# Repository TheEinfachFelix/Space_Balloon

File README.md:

# Space_Balloon

`git submodule update --init --recursive`

https://meshtastic.org/de/docs/hardware/devices/heltec-automation/lora32/peripherals/

## Reticulum Repos

https://github.com/attermann/microReticulum
https://github.com/markqvist/reticulum

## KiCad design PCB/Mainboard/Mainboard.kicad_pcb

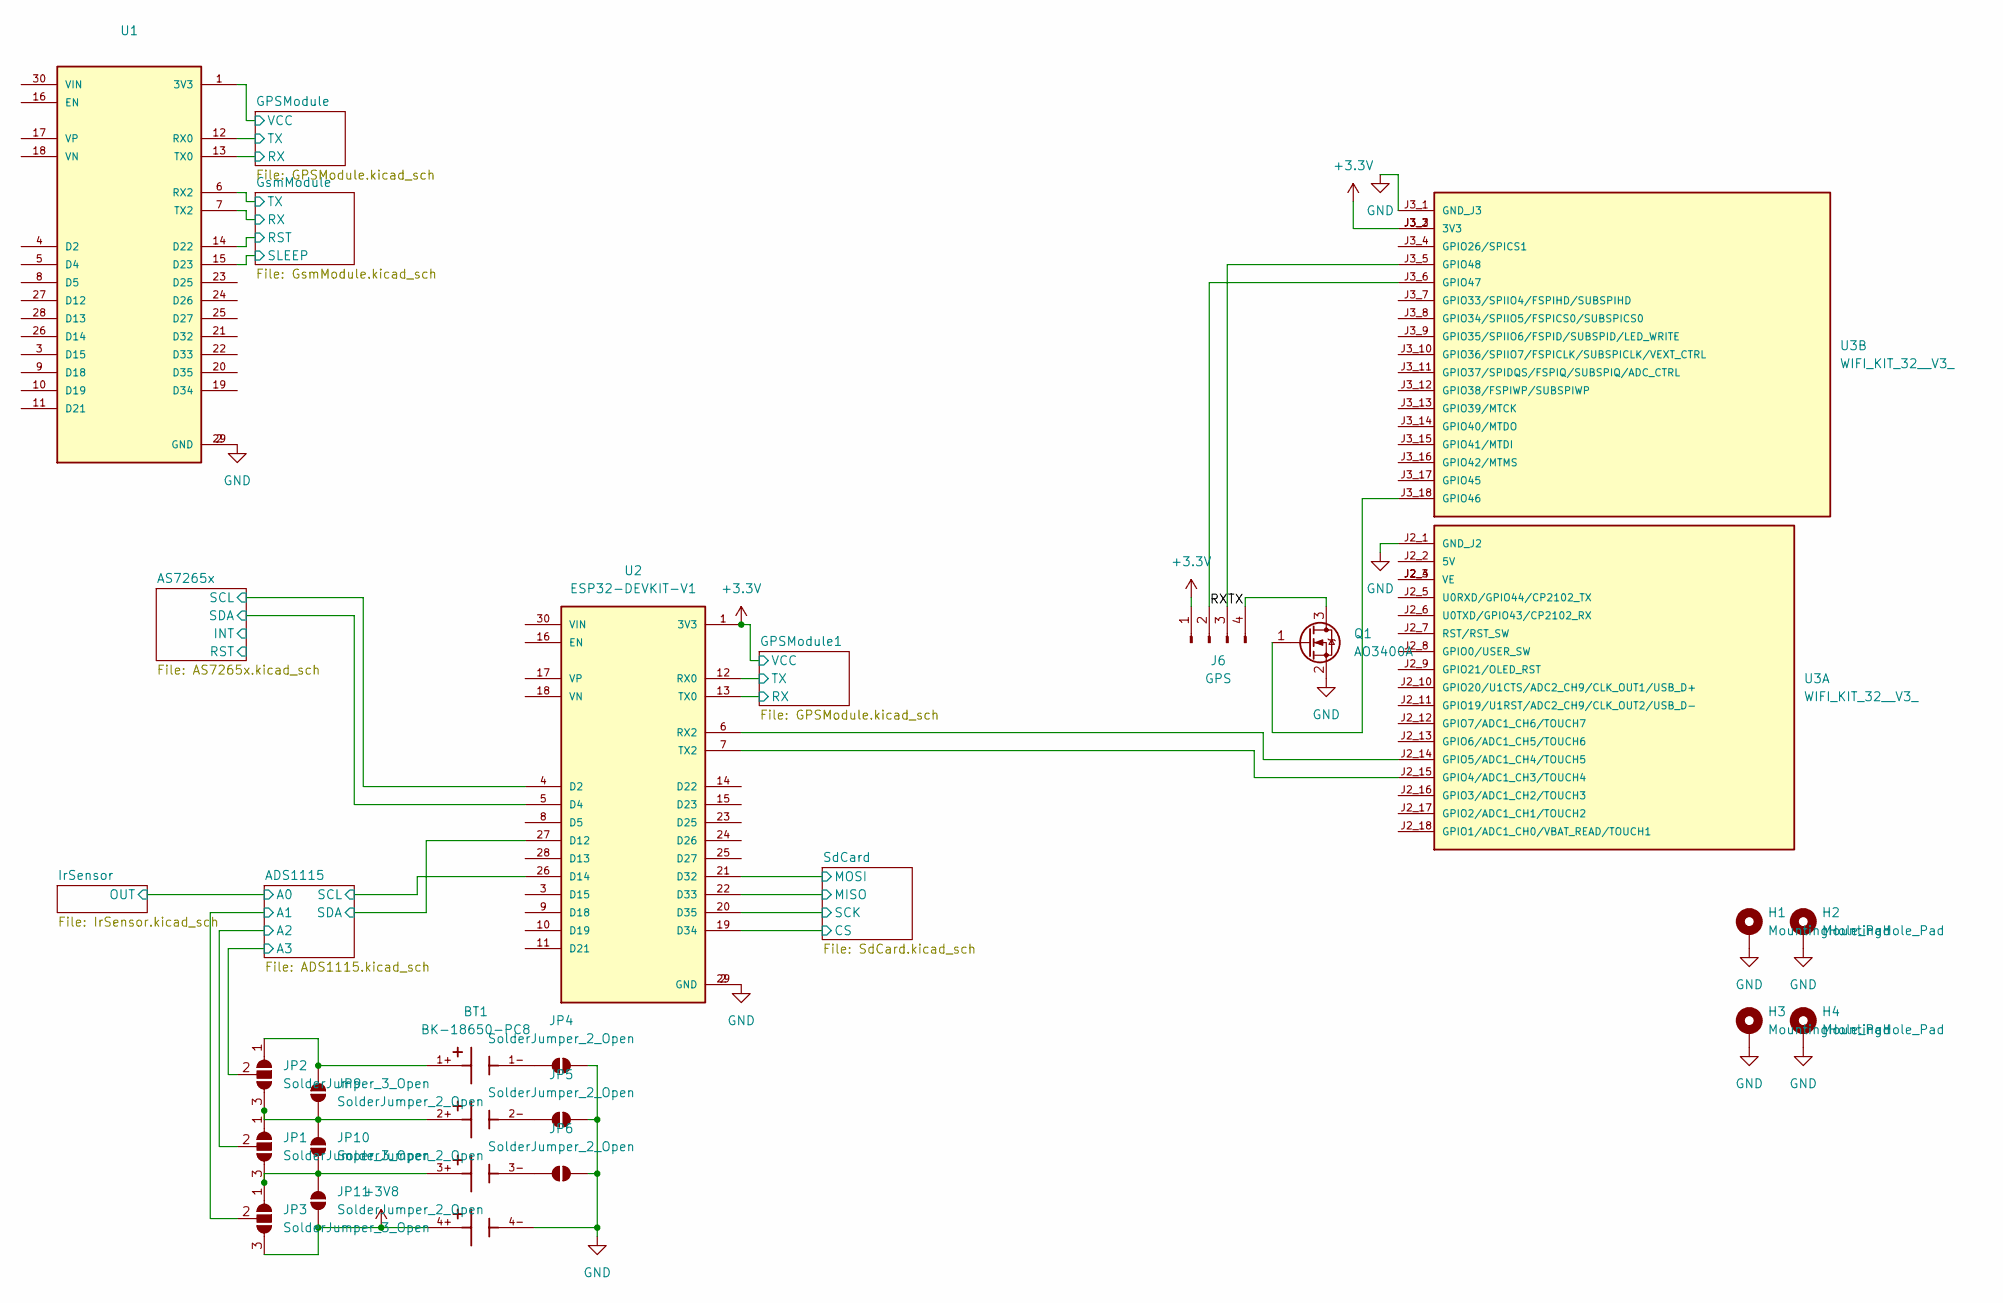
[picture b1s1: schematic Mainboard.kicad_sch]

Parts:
BT1: BK-18650-PC8; BAT_BK-18650-PC8
H1, H2, H3, H4: MountingHole_Pad; MountingHole_3.2mm_M3_Pad
J6: GPS; PinHeader_1x04_P2.54mm_Vertical
JP1, JP2, JP3: SolderJumper_3_Open; SolderJumper-3_P2.0mm_Open_TrianglePad1.0x1.5mm_NumberLabels
JP4, JP5, JP6, JP9, JP10, JP11: SolderJumper_2_Open; SolderJumper-2_P1.3mm_Open_TrianglePad1.0x1.5mm
Q1: AO3400A; SOT-23
U1, U2: ESP32-DEVKIT-V1; MODULE_ESP32_DEVKIT_V1_NO_WIFI_No_Hole; PARTREV N/A
U3: WIFI_KIT_32__V3_; MODULE_WIFI_KIT_32__V3_; PARTREV Rev 1.1

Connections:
+3.3V: J6.1, U2.1 (3V3), U3.J3_2 (3V3), U3.J3_3 (3V3); also elsewhere on the board
+3V8: BT1.4+, JP3.3 (B), JP11.1 (A); also elsewhere on the board
/ADS1115/A1: JP3.2 (C); also elsewhere on the board
/ADS1115/A2: JP1.2 (C); also elsewhere on the board
/ADS1115/A3: JP2.2 (C); also elsewhere on the board
/ADS1115/SCL: U2.26 (D14); also elsewhere on the board
/ADS1115/SDA: U2.27 (D12); also elsewhere on the board
/AS7265x/SCL: U2.4 (D2); also elsewhere on the board
/AS7265x/SDA: U2.5 (D4); also elsewhere on the board
/GPSModule1/RX: U2.13 (TX0); also elsewhere on the board
/GPSModule1/TX: U2.12 (RX0); also elsewhere on the board
/GPSModule/RX: U1.13 (TX0); also elsewhere on the board
/GPSModule/TX: U1.12 (RX0); also elsewhere on the board
/GPSModule/VCC: U1.1 (3V3); also elsewhere on the board
/GsmModule/RST: U1.14 (D22); also elsewhere on the board
/GsmModule/RX: U1.7 (TX2); also elsewhere on the board
/GsmModule/SLEEP: U1.15 (D23); also elsewhere on the board
/GsmModule/TX: U1.6 (RX2); also elsewhere on the board
/RX: J6.2, U3.J3_6 (GPIO47)
/SdCard/CS: U2.19 (D34); also elsewhere on the board
/SdCard/MISO: U2.22 (D33); also elsewhere on the board
/SdCard/MOSI: U2.21 (D32); also elsewhere on the board
/SdCard/SCK: U2.20 (D35); also elsewhere on the board
/TX: J6.3, U3.J3_5 (GPIO48)
GND: BT1.4-, H1.1, H2.1, H3.1, H4.1, JP4.2 (B), JP5.2 (B), JP6.2 (B), Q1.2 (S), U1.2 (GND), U1.29 (GND), U2.2 (GND), U2.29 (GND), U3.J2_1 (GND_J2), U3.J3_1 (GND_J3); also elsewhere on the board
unnamed: J6.4, Q1.3 (D)
unnamed: BT1.2+, JP1.1 (A), JP2.3 (B), JP9.1 (A), JP10.2 (B)
unnamed: BT1.3+, JP1.3 (B), JP3.1 (A), JP10.1 (A), JP11.2 (B)
unnamed: BT1.1+, JP2.1 (A), JP9.2 (B)
unnamed: BT1.1-, JP4.1 (A)
unnamed: BT1.2-, JP5.1 (A)
unnamed: BT1.3-, JP6.1 (A)
unnamed: Q1.1 (G), U3.J3_18 (GPIO46)
unnamed: U2.6 (RX2), U3.J2_14 (GPIO5/ADC1_CH4/TOUCH5)
unnamed: U2.7 (TX2), U3.J2_15 (GPIO4/ADC1_CH3/TOUCH4)
unnamed: U3.J2_3 (VE), U3.J2_4 (VE)

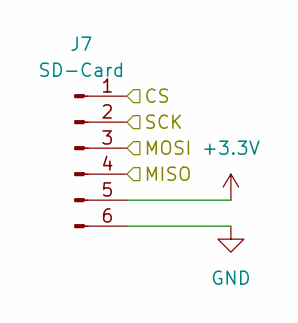
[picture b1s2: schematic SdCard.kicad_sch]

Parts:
J7: SD-Card; PinHeader_1x06_P2.54mm_Vertical

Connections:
+3.3V: J7.5; also elsewhere on the board
/SdCard/CS: J7.1; also elsewhere on the board
/SdCard/MISO: J7.4; also elsewhere on the board
/SdCard/MOSI: J7.3; also elsewhere on the board
/SdCard/SCK: J7.2; also elsewhere on the board
GND: J7.6; also elsewhere on the board

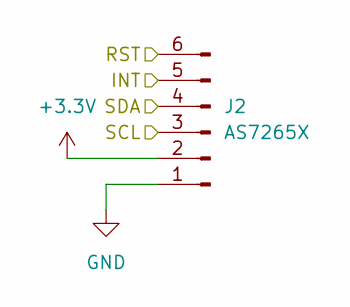
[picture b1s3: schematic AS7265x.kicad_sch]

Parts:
J2: AS7265X; PinHeader_1x06_P2.54mm_Vertical

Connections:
+3.3V: J2.2; also elsewhere on the board
/AS7265x/INT: J2.5
/AS7265x/RST: J2.6
/AS7265x/SCL: J2.3; also elsewhere on the board
/AS7265x/SDA: J2.4; also elsewhere on the board
GND: J2.1; also elsewhere on the board

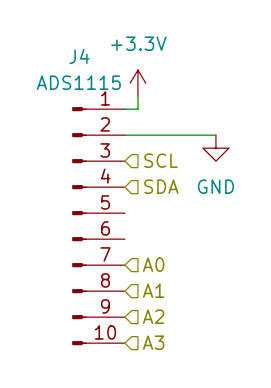
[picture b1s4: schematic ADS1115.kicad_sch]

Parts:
J4: ADS1115; PinHeader_1x10_P2.54mm_Vertical

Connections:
+3.3V: J4.1; also elsewhere on the board
/ADS1115/A0: J4.7; also elsewhere on the board
/ADS1115/A1: J4.8; also elsewhere on the board
/ADS1115/A2: J4.9; also elsewhere on the board
/ADS1115/A3: J4.10; also elsewhere on the board
/ADS1115/SCL: J4.3; also elsewhere on the board
/ADS1115/SDA: J4.4; also elsewhere on the board
GND: J4.2; also elsewhere on the board

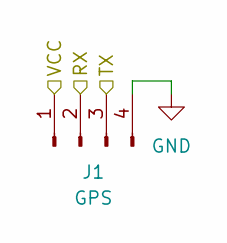
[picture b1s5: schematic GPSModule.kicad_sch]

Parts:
J1: GPS; PinHeader_1x04_P2.54mm_Vertical

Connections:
/GPSModule/RX: J1.2; also elsewhere on the board
/GPSModule/TX: J1.3; also elsewhere on the board
/GPSModule/VCC: J1.1; also elsewhere on the board
GND: J1.4; also elsewhere on the board

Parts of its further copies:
J5: GPS; PinHeader_1x04_P2.54mm_Vertical

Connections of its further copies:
+3.3V: J5.1; also elsewhere on the board
/GPSModule1/RX: J5.2; also elsewhere on the board
/GPSModule1/TX: J5.3; also elsewhere on the board
GND: J5.4; also elsewhere on the board

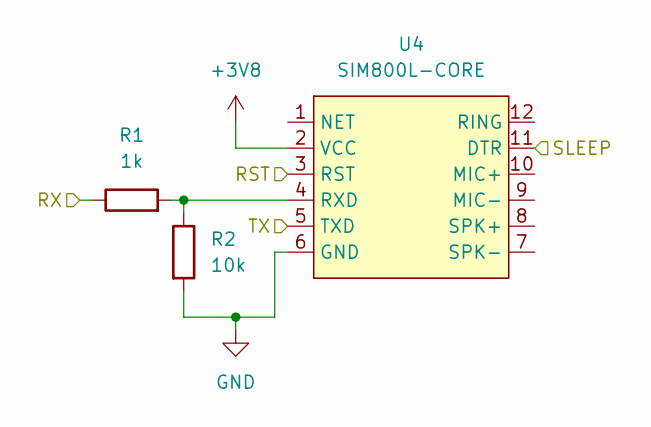
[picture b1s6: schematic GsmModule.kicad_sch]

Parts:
R1: 1k; R_Axial_DIN0411_L9.9mm_D3.6mm_P15.24mm_Horizontal
R2: 10k; R_Axial_DIN0411_L9.9mm_D3.6mm_P15.24mm_Horizontal
U4: SIM800L-CORE

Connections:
+3V8: U4.2 (VCC); also elsewhere on the board
/GsmModule/RST: U4.3 (RST); also elsewhere on the board
/GsmModule/RX: R1.1; also elsewhere on the board
/GsmModule/SLEEP: U4.11 (DTR); also elsewhere on the board
/GsmModule/TX: U4.5 (TXD); also elsewhere on the board
GND: R2.2, U4.6 (GND); also elsewhere on the board
unnamed: R1.2, R2.1, U4.4 (RXD)

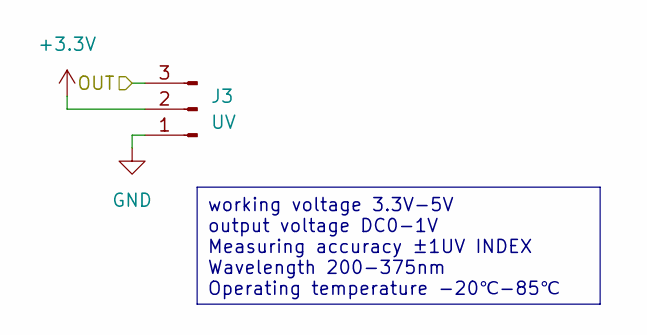
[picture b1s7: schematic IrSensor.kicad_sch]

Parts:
J3: UV; PinHeader_1x03_P2.54mm_Vertical

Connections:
+3.3V: J3.2; also elsewhere on the board
/ADS1115/A0: J3.3; also elsewhere on the board
GND: J3.1; also elsewhere on the board

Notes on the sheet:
working voltage 3.3V-5V output voltage DC0-1V Measuring accuracy ±1UV INDEX Wavelength 200-375nm Operating temperature -20℃-85℃

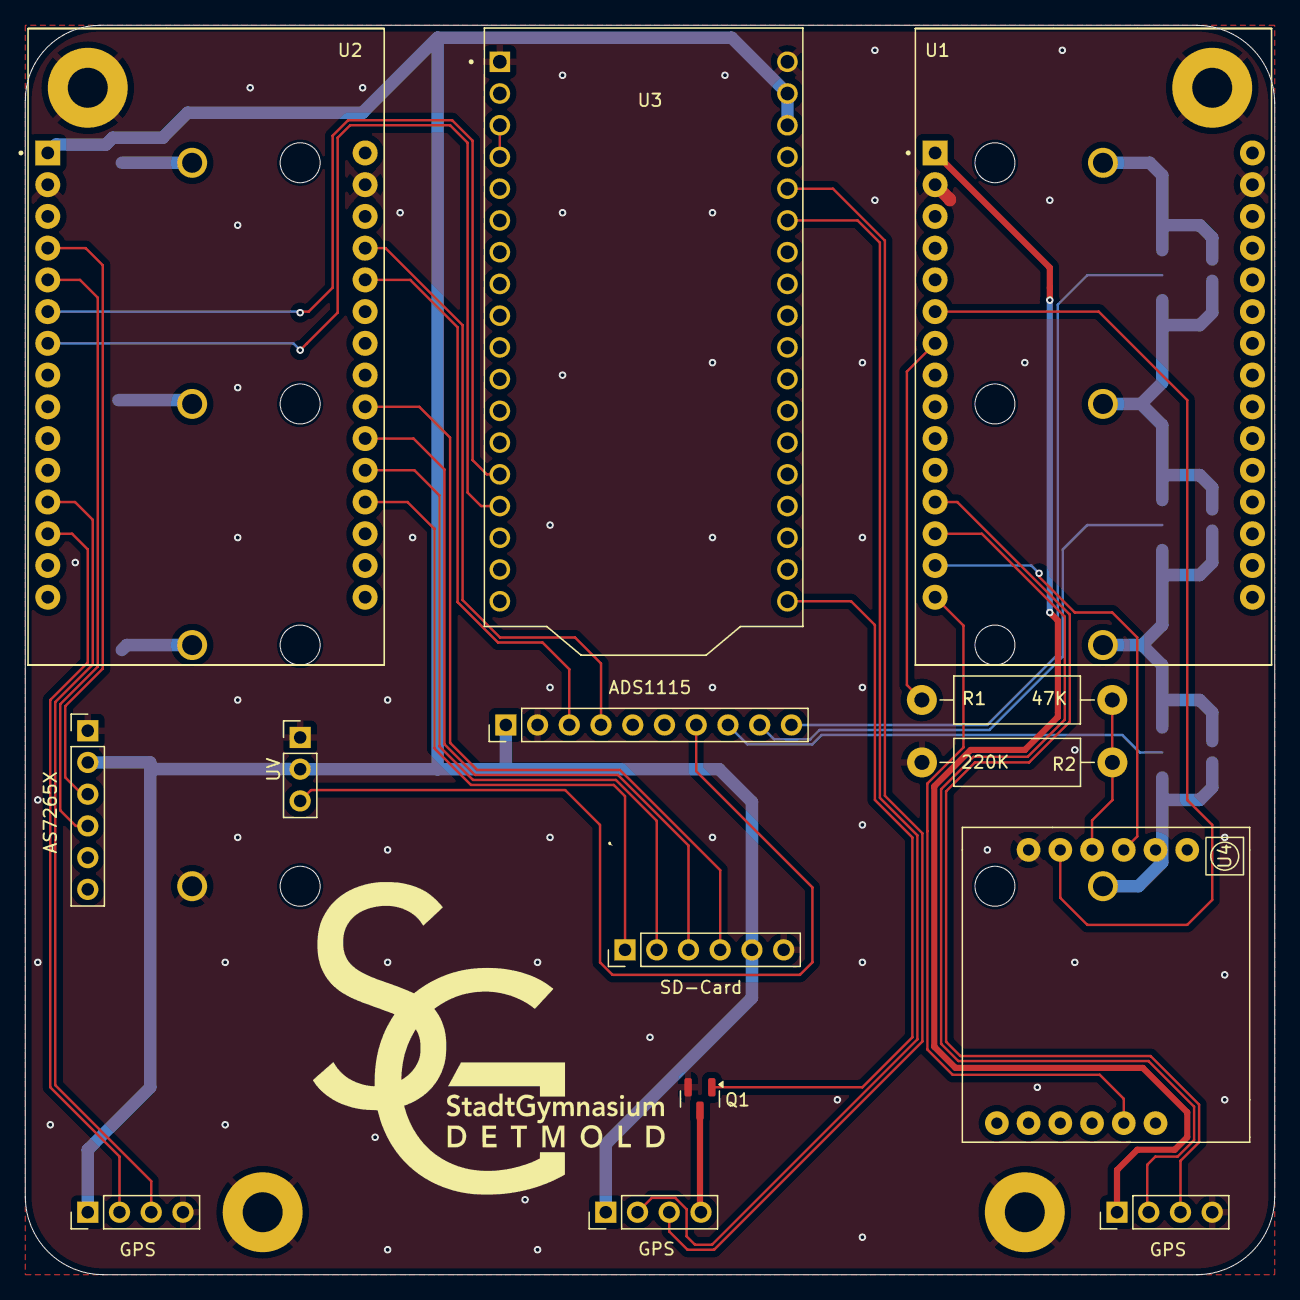
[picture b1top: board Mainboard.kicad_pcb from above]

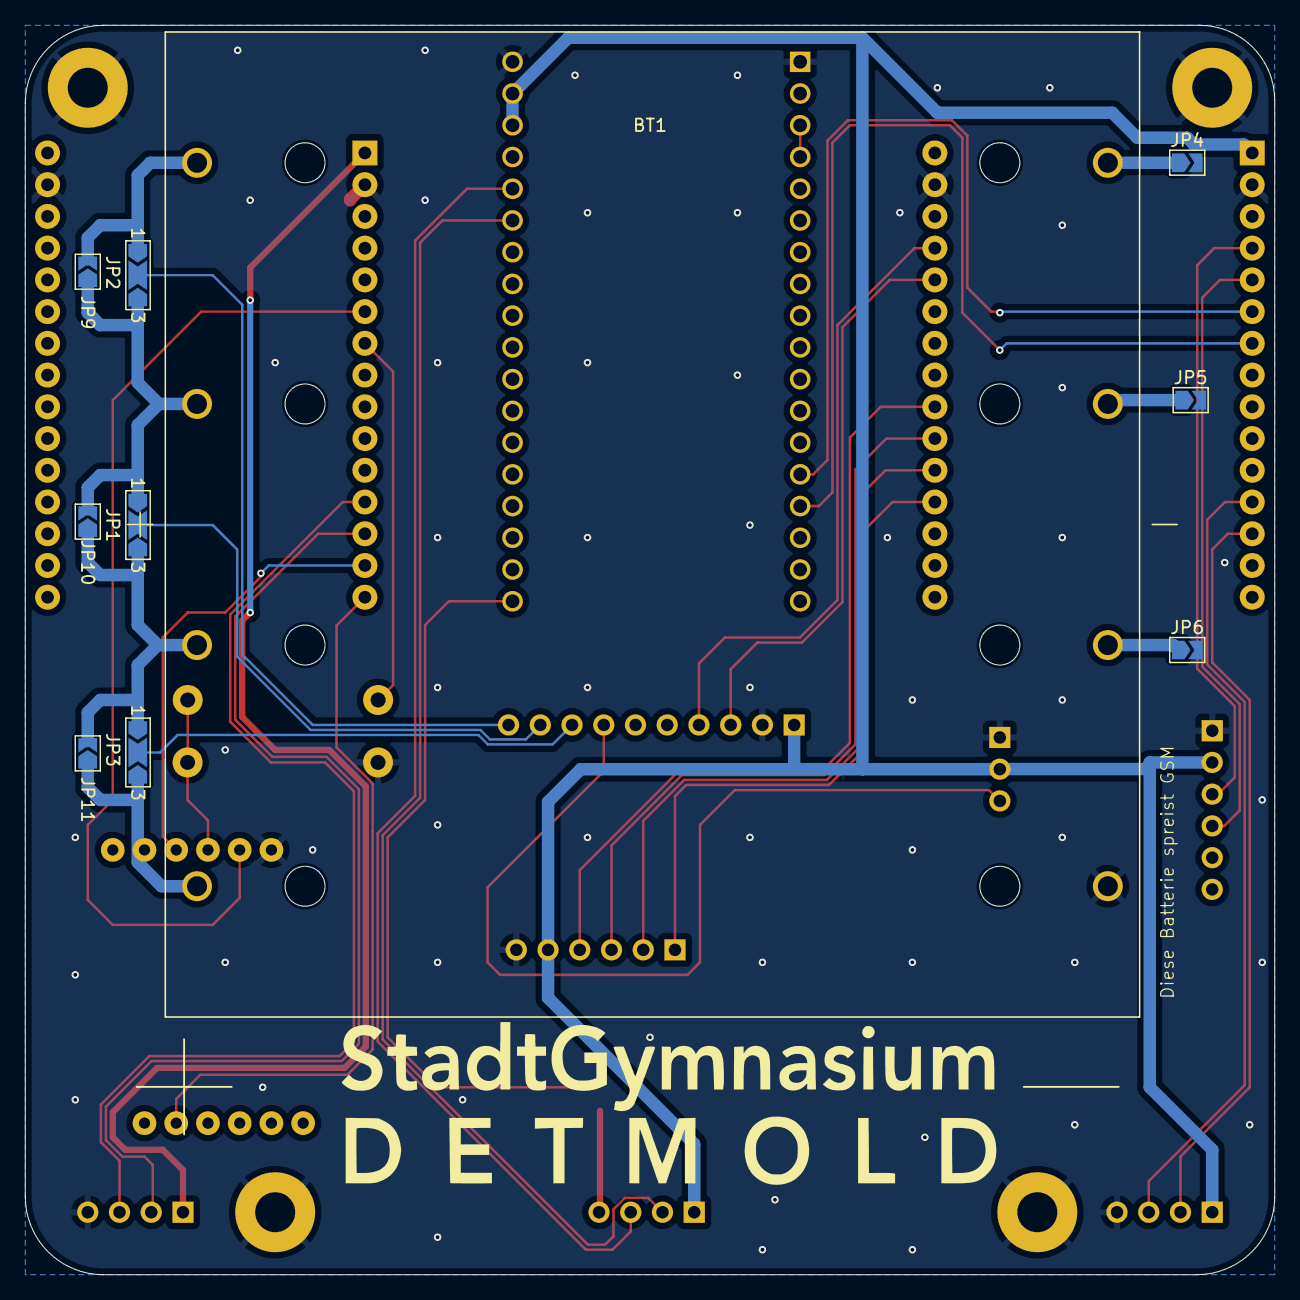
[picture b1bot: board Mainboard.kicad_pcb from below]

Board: 2 copper layers, 100.0 x 100.0 mm, 28 parts (10 on the bottom side), 38 nets.

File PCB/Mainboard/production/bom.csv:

Designator,Footprint,Quantity,Value,LCSC Part #
BT1,BAT_BK-18650-PC8,1,BK-18650-PC8,
"J1, J5, J6",PinHeader_1x04_P2.54mm_Vertical,3,GPS,
J2,PinHeader_1x06_P2.54mm_Vertical,1,AS7265X,
J3,PinHeader_1x03_P2.54mm_Vertical,1,UV,
J4,PinHeader_1x10_P2.54mm_Vertical,1,ADS1115,
J7,PinHeader_1x06_P2.54mm_Vertical,1,SD-Card,
Q1,SOT-23,1,AO3400A,
R1,R_Axial_DIN0411_L9.9mm_D3.6mm_P15.24mm_Horizontal,1,47K,
R2,R_Axial_DIN0411_L9.9mm_D3.6mm_P15.24mm_Horizontal,1,220K,
"U1, U2",MODULE_ESP32_DEVKIT_V1_NO_WIFI_No_Hole,2,ESP32-DEVKIT-V1,
U3,MODULE_WIFI_KIT_32__V3_,1,WIFI_KIT_32__V3_,
U4,SIM800L-CORE,1,SIM800L-CORE,

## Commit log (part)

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2025-08-16 Startetd with the PCB Scematic
2025-08-19 First rev is done
2025-08-20 rouned the corners
2025-08-24 added a label
2025-09-04 Wrote some Doku
2025-09-18 started with the gsm code
2025-09-18 changed the submodule
2025-09-18 Remove old submodule entry
2025-09-18 done
2025-09-30 fixed it
2025-10-01 Setup the projekt
2025-10-02 updated some resitor values
2025-10-02 implemented the first features
2025-10-03 Changes Submodule
2025-10-03 stuff
2025-10-04 worked on the new lib
2025-10-04 Added Sleep
2025-10-07 Code is alemost done
2025-10-07 messed with GPS
2025-10-08 GPS is now working
2025-10-08 rm lck
2025-10-08 Fixed readme
2025-10-09 added diagramm
2026-02-15 fixed imports
